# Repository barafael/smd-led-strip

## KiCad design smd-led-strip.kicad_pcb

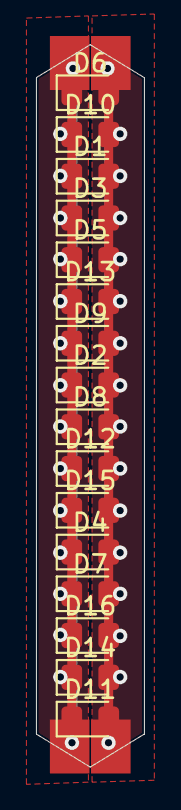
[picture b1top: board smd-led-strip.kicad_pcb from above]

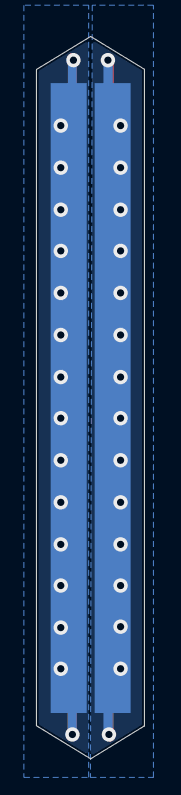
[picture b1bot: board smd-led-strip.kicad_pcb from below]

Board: 2 copper layers, 6.0 x 40.1 mm, 22 parts (2 on the bottom side), 2 nets.

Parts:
D1, D2, D3, D4, D5, D6, D7, D8, D9, D10, D11, D12, D13, D14, D15, D16: LED; LED_0805_2012Metric_Pad1.15x1.40mm_HandSolder
J4, J4#2, J4#3, J4#4, J4#5, J4#6: heatsink; Pin_D1.0mm_L10.0mm_LooseFit

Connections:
GND: D1.1, D2.1, D3.1, D4.1, D5.1, D6.1, D7.1, D8.1, D9.1, D10.1, D11.1, D12.1, D13.1, D14.1, D15.1, D16.1, J4.1, J4#4.1, J4#5.1
VDD: D1.2, D2.2, D3.2, D4.2, D5.2, D6.2, D7.2, D8.2, D9.2, D10.2, D11.2, D12.2, D13.2, D14.2, D15.2, D16.2, J4#2.1, J4#3.1, J4#6.1

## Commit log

2021-02-10 Add image
